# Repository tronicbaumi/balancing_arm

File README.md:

# Balancing Arm

A human-arm-pose-controlled dual-motor system. A Raspberry Pi 5 uses computer vision to track a person's elbow angles in real time and sends those values over SPI to a microcontroller bridge, which forwards them over CAN bus to drone ESC boards that spin BLDC motors on a physical balance arm.

---

## System Architecture

```
┌──────────────────────┐        SPI (1 MHz)        ┌──────────────────────┐
│   Raspberry Pi 5     │ ─────────────────────────► │  dsPIC33CK1024MP710  │
│                      │    2-byte frame / 100 ms   │  (CAN/LIN Curiosity) │
│  YOLO11 pose model   │    [left_val, right_val]   │  SPI slave → CAN Tx  │
│  Pi Camera 2.1       │                            └──────────┬───────────┘
└──────────────────────┘                                       │
                                                               │ CAN 2.0
                                             ┌─────────────────┴─────────────────┐
                                             │                                   │
                                    ID 0x001 ▼                          ID 0x002 ▼
                               ┌─────────────────────┐        ┌─────────────────────┐
                               │  dsPIC33CDVC256MP506 │        │  dsPIC33CDVC256MP506 │
                               │  Drone ESC (Node 1) │        │  Drone ESC (Node 2) │
                               │  Sensorless FOC     │        │  Sensorless FOC     │
                               └────────┬────────────┘        └────────┬────────────┘
                                        │                               │
                                   Left Motor                     Right Motor
                                 (Ducted Fan BLDC)             (Ducted Fan BLDC)
```

**Data flow:**
1. Camera captures the user's pose at 1280×720.
2. YOLO11n-pose extracts left/right elbow angles (60°–150° mapped to 0–255).
3. Pi sends a 2-byte SPI frame every 100 ms.
4. Bridge board splits the frame and transmits two CAN messages (ID 0x001, ID 0x002).
5. Each ESC reads its CAN ID, maps the byte to motor speed via `(255 - angle) << 5`, and drives the motor with sensorless FOC.

---

## Repository Structure

```
balancing_arm/
├── fw/
│   ├── rpi5/                   Python vision app (Raspberry Pi 5)
│   ├── ctrlBoard2/             Bridge board firmware (dsPIC33CK — SPI slave / CAN master)
│   └── droneESC/               ESC firmware (dsPIC33CDVC — CAN slave / motor drive)
├── hw/
│   ├── KiCad/                  Custom ESC PCB schematic and layout
│   └── 04-12307-dspic33cdvc-drone-esc-reference-design-Rev2.0/  Altium reference design
├── mec/
│   └── balance/                3D-printable mechanical parts (OpenSCAD + STL + 3MF)
├── doc/                        Datasheets, user guides, motor calculations
└── sw/                         (reserved)
```

---

## Hardware

| Board | MCU | Role |
|---|---|---|
| Raspberry Pi 5 | — | Vision node / SPI master |
| dsPIC33C Touch CAN LIN Curiosity (EV97U97A) | dsPIC33CK1024MP710 | SPI slave → CAN bridge |
| Drone ESC (custom KiCad / Pallas ref design) | dsPIC33CDVC256MP506 | CAN slave / BLDC drive |

**Communication:**

| Link | Protocol | Details |
|---|---|---|
| Pi → Bridge | SPI Mode 1, 1 MHz | 2-byte frame, `[left, right]`, every 100 ms |
| Bridge → ESC | CAN 2.0 standard, DLC=1 | Left arm → ID 0x001, right arm → ID 0x002 |
| ESC → Gate driver | Single-wire UART (DE2) | MCP8021, 9600 baud |

---

## Firmware

### `fw/rpi5/` — Raspberry Pi 5 (Python)

Runs YOLO11n-pose on a live camera feed to extract elbow angles and streams them over SPI.

**Dependencies:**
```
picamera2
ultralytics
opencv-python
spidev
numpy
```

**Run:**
```bash
cd fw/rpi5
source .venv/bin/activate
python "Core Pose Estimation Collection/claude10.py"
```

The script:
- Opens the Pi Camera 2 at 1280×720 RGB.
- Runs `YOLO11n-pose.pt` inference at 320 px input size.
- Computes elbow angles from COCO keypoints (shoulder–elbow–wrist triplets).
- Maps angles to bytes and sends a 2-byte SPI frame (CE0 / GPIO8) every 100 ms.
- Displays an annotated live preview with angle and value overlays.

### `fw/ctrlBoard2/` — Bridge Board Firmware (MPLAB X / XC16)

Project: `dspic33c-touch-can-lin-curiosity-oob-1.0.2`

Receives 2-byte SPI frames as a client and transmits two CAN 2.0 messages.

**Build:** Open `dspic33c-touch-can-lin-curiosity-oob-1.0.2.X` in MPLAB X IDE and build with XC16.

**Key files:**
- `application/application.c` — SPI receive + CAN transmit logic
- `mcc_generated_files/` — MCC Melody peripherals (SPI1, CAN1, TMR1, UART1, ADC)

**DFP:** `dsPIC33CK-MP_DFP v1.13.366`

### `fw/droneESC/` — Drone ESC Firmware (MPLAB X / XC16)

Project: `cdvc_drone_duct_can.X`

Receives a CAN message on its assigned node ID and sets motor speed using sensorless FOC.

**Build:** Open `cdvc_drone_duct_can.X` in MPLAB X IDE and build with XC16.

**Key files:**
- `main.c` — startup, CAN enable, motor start (2000 RPM after 5 s delay)
- `APL_CAN.c` / `APL_CAN.h` — CAN receive and `MCAPI_VelocityReferenceSet()` call
- `mcc_generated_files/motorBench/` — MCAF R9/RC31 sensorless FOC (ATPLL estimator, PI current/speed loops)

**Configure node ID** in `APL_CAN.h`:
```c
#define ARM_CAN_NODE  1   // 1 = left arm (ID 0x001), 2 = right arm (ID 0x002)
```

**Motor parameters (ducted fan):**
- 6-pole BLDC, R = 80.9 mΩ, L = 2.51 µH
- Ke = 5.63 mV/(rad/s), max 24 kRPM, rated 11 A
- 20 kHz PWM, CAN transceiver: ATA6563, gate driver: MCP8021

**DFP:** `dsPIC33CD-MP_DFP v1.2.151`

---

## Hardware Design

### `hw/KiCad/`

Custom ESC PCB (`EVXXXX_02-01243_Drone_ESC_Ref_Design`) with:
- Sheet 2: Inverter gate driver
- Sheet 3: Sense circuits and programming interface
- Sheet 4: CAN interface (ATA6563)

Open with **KiCad 8**.

### `hw/04-12307-.../`

Altium Designer reference design for the dsPIC33CDVC drone ESC. Includes schematic, PCB, and BOM.

---

## Mechanical Design

All parts are in `mec/balance/` as parameterized OpenSCAD files with pre-exported STL and 3MF.

| File | Description |
|---|---|
| `balance.scad` | Center hub — connects two 65 mm arm tubes, 8.1 mm pivot bore |
| `balance_base.scad` | Vertical stand — 80×180 mm base, 160 mm tall, 22 mm bearing pockets |
| `propmount.scad` | Propeller/fan mount — 66 mm fan, 20 mm motor bore, cable routing |

Print at standard FDM settings. Requires an 8–10 mm steel axle and 22 mm bearings.

---

## Tools Required

| Tool | Version | Purpose |
|---|---|---|
| MPLAB X IDE | 6.x | Build and program dsPIC firmware |
| XC16 Compiler | Latest | C compiler for dsPIC33 |
| MCC Melody | Bundled | Peripheral code generation |
| motorBench | R9 / RC31 | FOC motor tuning and code generation |
| X2Cscope | — | Real-time variable watch / oscilloscope over CAN/UART |
| Python | 3.10+ | RPi 5 vision app |
| KiCad | 8 | Custom ESC PCB |
| OpenSCAD | Latest | Mechanical part editing |

---

## Development Branch

Active branch: `develop_can` — CAN integration work.

```
main           ← stable
develop        ← general development
develop_can    ← current (CAN integration)
```

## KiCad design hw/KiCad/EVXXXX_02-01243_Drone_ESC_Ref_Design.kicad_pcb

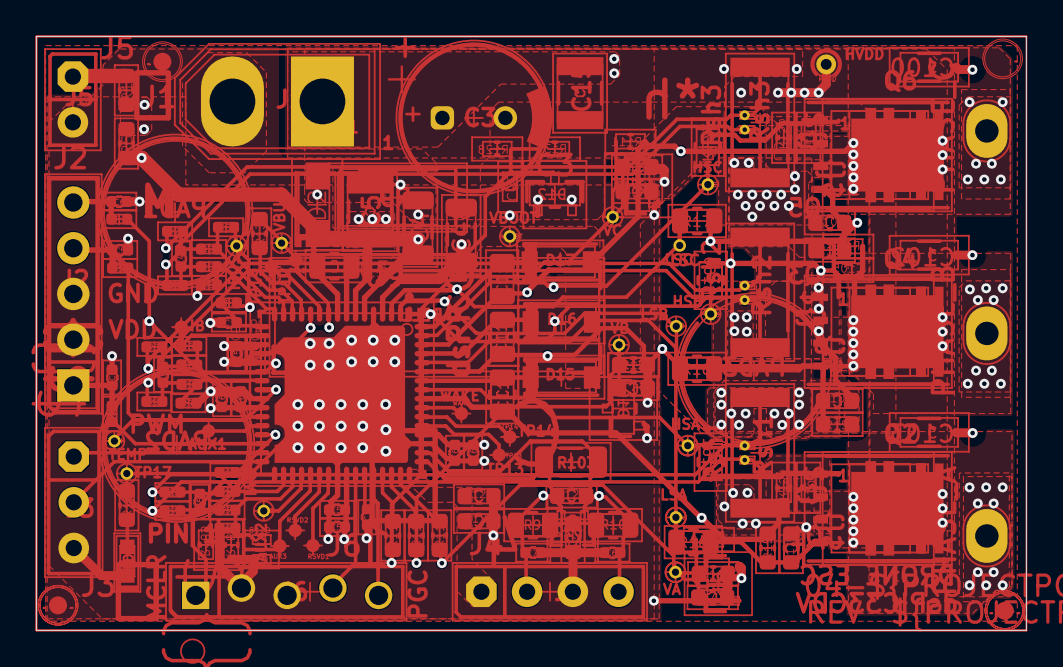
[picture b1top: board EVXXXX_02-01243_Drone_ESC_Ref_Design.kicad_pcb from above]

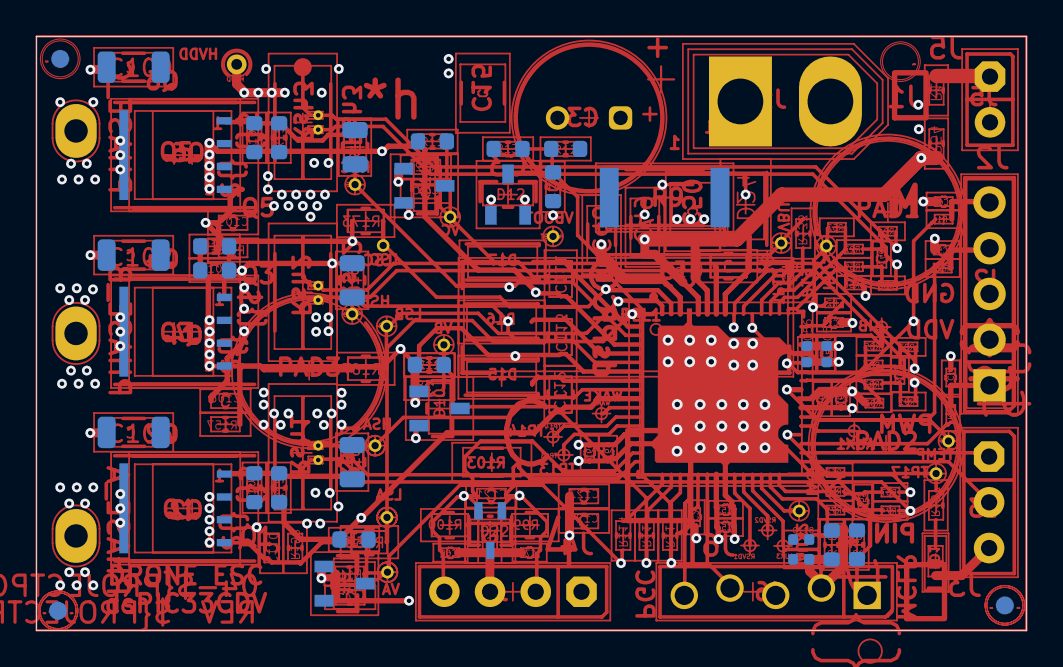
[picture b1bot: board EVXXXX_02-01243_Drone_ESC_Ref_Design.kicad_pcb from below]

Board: 4 copper layers, 55.0 x 33.0 mm, 174 parts (40 on the bottom side), 90 nets.

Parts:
AUX1, AUX3: Test Point No BOM; CON_TP_SMD_D25mil_NoSilk
AUX2: Test Point No BOM; TP_TH_0.7PADX0.4HOLE
C1, C2, C4, C5, C6, C39, C46, C53, C54, C55, C56, C57, C58, C60, C61, C62, C63, C65, C69, C71, C118: Capacitor NP; CAP_C_0402
C3: Capacitor POL; CAP_RAD_P3.5D8H13_WE
C15, C50: Capacitor NP; CAP_C_1210
C48, C49, C100, C102, C103: Capacitor NP; CAP_C_1206
C51, C111, C112, C113: Capacitor NP; CAP_C_0805
C70, C75, C76, C78, C85, C105, C106, C107, C108, C109, C110, C121, C123, C124: Capacitor NP; CAP_C_0603
D9, D10, D11, D12: Diode Schottky Dual AK; SOT-23-3
D15, D16, D17: Diode Schottky; SOD-123
D22: Diode K1K2CC ESD Bidirectional; SOT-323-3
D24: Diode Schottky; SOD-123W
FD1, FD2, FD3, FD4, FD5, FD6: FIDUCIAL ROUND; Fiducial_1mm
HSA: Test Point No BOM; TP_TH_0.7PADX0.4HOLE
HSB: Test Point No BOM; TP_TH_0.7PADX0.4HOLE
HSC: Test Point No BOM; TP_TH_0.7PADX0.4HOLE
HVDD: Test Point No BOM; TP_1.1x0.6
IA: Test Point No BOM; CON_TP_SMD_D25mil_NoSilk
IB: Test Point No BOM; CON_TP_SMD_D25mil_NoSilk
IBUS: Test Point No BOM; TP_TH_0.7PADX0.4HOLE
J1: CON 1x2 POLARIZED; CON TERMINAL XT30U-M 5mm 1x2 Male 30A TH V
J2: Header 1x5; HDR_M_2.54_1x5_MH5.84_IH2.54_TH3.2_TH_VERT
J3: Header 1x3; HDR_M_2.54_1x3_TH_V_SAM_TSW-103-08-G-S
J4: Header 1x4; HDR_M_2.54_1x4
J5: Header 1x2; HDR_M_2.54_1x2_TH_V_SAM_TSW-102-08-G-S
J6: HDR_M_2.54_1x5_STAGGERED
LABEL1: 08-10015
LD1: LED_yellow; LED_0603_Yellow
LSA: Test Point No BOM; TP_TH_0.7PADX0.4HOLE
LSB: Test Point No BOM; TP_TH_0.7PADX0.4HOLE
LSC: Test Point No BOM; TP_TH_0.7PADX0.4HOLE
NT1, NT2, NT3, NT4, NT5, NT6: Net Tie; NET_TIE_0.2mmx0.5mm
PAD1, PAD2, PAD3: Rubber Pad Cylindrical; BUMP_3M_SJ61A1_CYLINDRICAL_BLACK_D7.9H5.08
PHASE_A: Test Point No BOM; TP_3.0X2.3X1.3HOLE
PHASE_B: Test Point No BOM; TP_3.0X2.3X1.3HOLE
PHASE_C: Test Point No BOM; TP_3.0X2.3X1.3HOLE
Q1, Q2, Q3, Q4, Q5, Q6: Transistor MOS-N SSSGD; PPAK_SO-8L
R1, R2, R11, R12, R21, R22, R52, R58, R59, R60, R67, R68, R69, R74, R75, R76, R83, R84, R85, R91, R92, R93: Resistor; RES_C_0402
R9: Resistor; RES_C_2512
R19, R110, R111, R112, R114, R115, R118, R119, R120, R121, R128, R133, R137, R153, R154, R156, R157, R158, R159, R181, R183, R187: Resistor; RES_C_0603
R54: RES_C_0603
R99, R100, R160, R161, R167, R168, R171, R173: Resistor; RES_C_0805
R103: Resistor; RES_C_1206
RSVD1, RSVD2: Test Point No BOM; CON_TP_SMD_D25mil_NoSilk
Rsh1, Rsh2, Rsh3: Resistor; RES_C_2512
TEMP: Test Point No BOM; TP_TH_0.7PADX0.4HOLE
TP12, TP13, TP14, TP19: Test Point No BOM; CON_TP_SMD_D25mil_NoSilk
TP17: Test Point No BOM; TP_TH_0.7PADX0.4HOLE
U9: dsPIC33CDVC256MP506_VGQFN-64; QFN-64_9X9_3EP_M9
VA: Test Point No BOM; TP_TH_0.7PADX0.4HOLE
VB: Test Point No BOM; TP_TH_0.7PADX0.4HOLE
VBOOT: Test Point No BOM; TP_TH_0.7PADX0.4HOLE
VBUS: Test Point No BOM; TP_TH_0.7PADX0.4HOLE
VC: Test Point No BOM; TP_TH_0.7PADX0.4HOLE
WAKE: Test Point No BOM; CON_TP_SMD_D25mil_NoSilk

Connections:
+3.3V_EXT: J5.1, R19.2
+5V: C123.1, C124.2, J4.1, U9.48
AD_PWM_IN1: R11.2, U9.30
AD_PWM_IN2: R12.2, U9.27
AUX1: AUX1.1, U9.28
AUX2: AUX2.1, U9.36
AUX3: AUX3.1, U9.37
GND: C1.2, C2.1, C3.2, C4.1, C5.1, C6.1, C15.1, C39.1, C48.2, C49.2, C50.1, C53.1, C54.1, C56.1, C57.1, C58.1, C60.1, C61.1, C62.1, C63.1, C69.2, C70.1, C71.2, C75.1, C76.1, C78.1, C85.1, C100.2, C102.2, C103.2, C118.1, C123.2, C124.1, D9.1, D10.1, D11.1, D12.1, D22.3, D24.1, J1.2, J2.3, J3.3, J4.3, J5.2, J6.3, LD1.2, NT6.2, R119.2, R120.2, R121.2, R137.2, Rsh3.1, U9.5, U9.20, U9.26, U9.40, U9.51, U9.65, U9.66, U9.67
HS_GATE_A: C106.2, Q1.4, R154.1, R161.2
HS_GATE_B: C105.2, Q3.4, R156.1, R160.2
HS_GATE_C: C107.2, Q5.4, R153.1, R171.2
HVDD: C50.2, R9.2, U9.7
IA: IA.1, R69.2, U9.33
IB: IB.1, R85.2, U9.18
IBUS: IBUS.1, R2.1, R52.2, U9.14
LED: R187.1, TP17.1, U9.29
LS_GATE_A: C110.2, Q2.4, R158.1, R168.2
LS_GATE_B: C108.2, Q4.4, R157.1, R167.2
LS_GATE_C: C109.2, Q6.4, R159.1, R173.2
NetC1_1: C1.1, R2.2, U9.17
NetC4_2: C4.2, J2.1, R11.1
NetC5_2: C5.2, J2.4, R12.1
NetC6_2: C6.2, J2.5, R1.1
NetC46_1: C46.1, R58.2, R59.1
NetC46_2: C46.2, R21.2, R22.1
NetC51_1: C51.1, U9.8
NetC51_2: C51.2, D24.2, U9.9
NetC55_1: C55.1, R74.2, R75.1
NetC55_2: C55.2, R67.2, R68.1
NetC65_1: C65.1, R91.2, R92.1
NetC65_2: C65.2, R83.2, R84.1
NetC70_2: C70.2, R99.1, R100.1
NetC75_2: C75.2, D9.3, R110.2, R114.1, R119.1, VA.1
NetC76_2: C76.2, D11.3, R111.2, R115.1, R120.1, VC.1
NetC78_2: C78.2, D10.3, R112.2, R118.1, R121.1, VB.1
NetC85_2: C85.2, D12.3, R128.2, R133.1, R137.1, VBUS.1
NetC108_1: C108.1, NT1.2, Q4.1, Q4.2, Q4.3, R157.2, Rsh2.2
NetC109_1: C109.1, NT3.2, NT4.2, NT5.2, Q6.1, Q6.2, Q6.3, R159.2, Rsh1.1, Rsh2.1, Rsh3.2
NetC110_1: C110.1, NT2.2, Q2.1, Q2.2, Q2.3, R158.2, Rsh1.2
NetC111_2: C111.2, D17.2, U9.64
NetC112_2: C112.2, D15.2, U9.58
NetC113_2: C113.2, D16.2, U9.61
NetC118_2: C118.2, R181.2, R183.1
NetHSA_1: HSA.1, R161.1, U9.57
NetHSB_1: HSB.1, R160.1, U9.60
NetHSC_1: HSC.1, R171.1, U9.63
NetLD1_1: LD1.1, R187.2
NetLSA_1: LSA.1, R168.1, U9.1
NetLSB_1: LSB.1, R167.1, U9.2
NetLSC_1: LSC.1, R173.1, U9.3
NetRSVD1_1: RSVD1.1, U9.39
NetRSVD2_1: RSVD2.1, U9.38
NetTP12_1: TP12.1, U9.10
NetTP13_1: TP13.1, U9.53
NetTP14_1: TP14.1, U9.54
NetTP19_1: TP19.1, U9.11
NetU9_55: U9.55, WAKE.1
OA1IN+: R59.2, R60.1, U9.16
OA1IN-: R22.2, R52.1, U9.15
OA2IN+: R75.2, R76.1, U9.35
OA2IN-: R68.2, R69.1, U9.34
OA3IN+: R92.2, R93.1, U9.23
OA3IN-: R84.2, R85.1, U9.22
PGC: J6.5, U9.44
PGD: J6.4, U9.42
PHASE_A: C106.1, C112.1, PHASE_A.1, Q1.1, Q1.2, Q1.3, Q2.5, R110.1, R154.2, U9.56
PHASE_B: C105.1, C113.1, PHASE_B.1, Q3.1, Q3.2, Q3.3, Q4.5, R112.1, R156.2, U9.59
PHASE_C: C107.1, C111.1, PHASE_C.1, Q5.1, Q5.2, Q5.3, Q6.5, R111.1, R153.2, U9.62
SHUNT_IA_N: NT3.1, R67.1
SHUNT_IA_P: NT2.1, R74.1
SHUNT_IBUS_N: NT6.1, R21.1
SHUNT_IBUS_P: NT4.1, R58.1
SHUNT_IB_N: NT5.1, R83.1
SHUNT_IB_P: NT1.1, R91.1
TEMP: TEMP.1, U9.24
UART_PWM: R1.2, U9.21
VA: R114.2, U9.47
VB: R118.2, U9.46
VBOOT: C48.1, D15.1, D16.1, D17.1, U9.4, VBOOT.1
VC: R115.2, U9.45
VDC: C3.1, C15.2, C100.1, C102.1, C103.1, HVDD.1, J1.1, Q1.5, Q3.5, Q5.5, R9.1, R128.1
VDD: C39.2, C53.2, C54.2, C56.2, C57.2, C58.2, C60.2, C61.2, C62.2, C63.2, D9.2, D10.2, D11.2, D12.2, J2.2, J6.2, R19.1, R54.2, R60.2, R76.2, R93.2, R181.1, U9.19, U9.25, U9.41, U9.52
VREG: C49.1, R54.1, U9.6
V_BUS: R133.2, U9.13
dsPIC_DEBUG_RX: J3.2, U9.32
dsPIC_DEBUG_TX: J3.1, U9.31
dsPIC_PIN_43: C2.2, U9.43
dsPIC_PIN_49: C71.1, C121.1, D22.1, J4.2, R99.2, R103.1, U9.49
dsPIC_PIN_50: C69.1, C121.2, D22.2, J4.4, R100.2, R103.2, U9.50
~MCLR: J6.1, R183.2, U9.12

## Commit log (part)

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2026-06-12 projects added
2026-06-12 minor
2026-06-15 droneESC update
